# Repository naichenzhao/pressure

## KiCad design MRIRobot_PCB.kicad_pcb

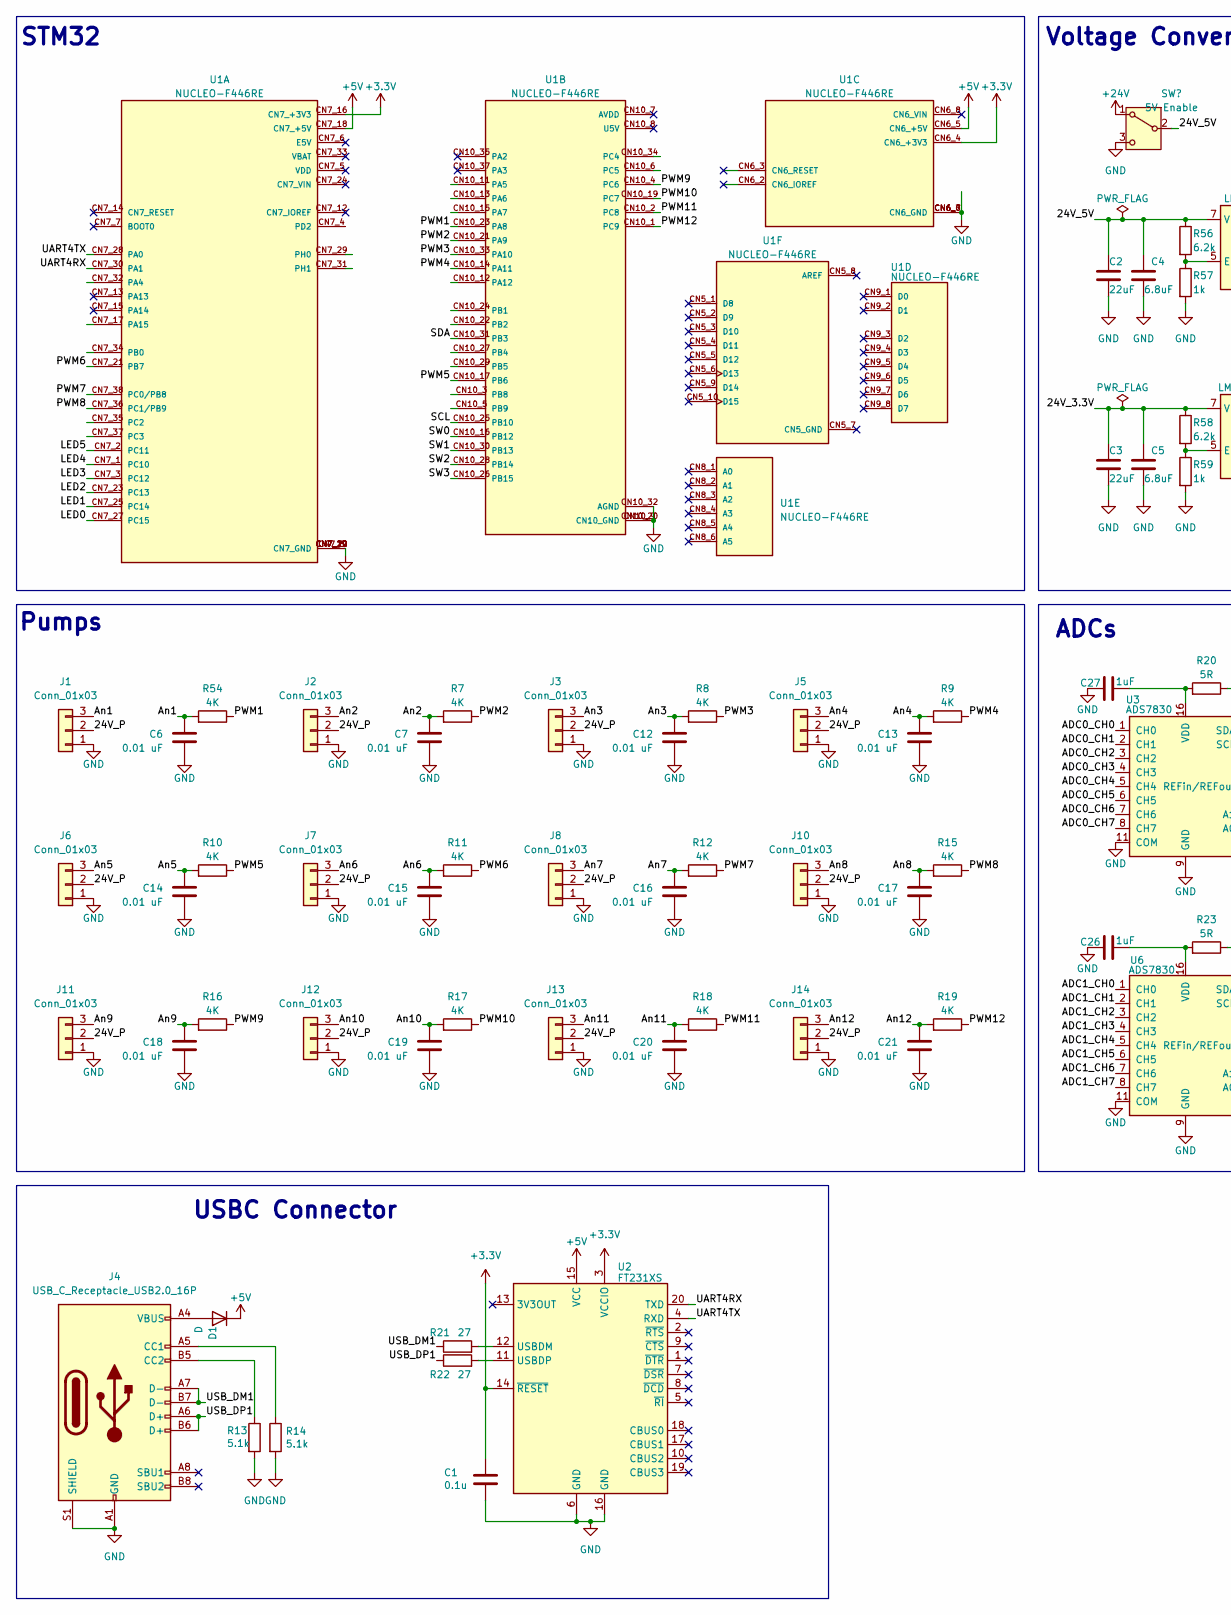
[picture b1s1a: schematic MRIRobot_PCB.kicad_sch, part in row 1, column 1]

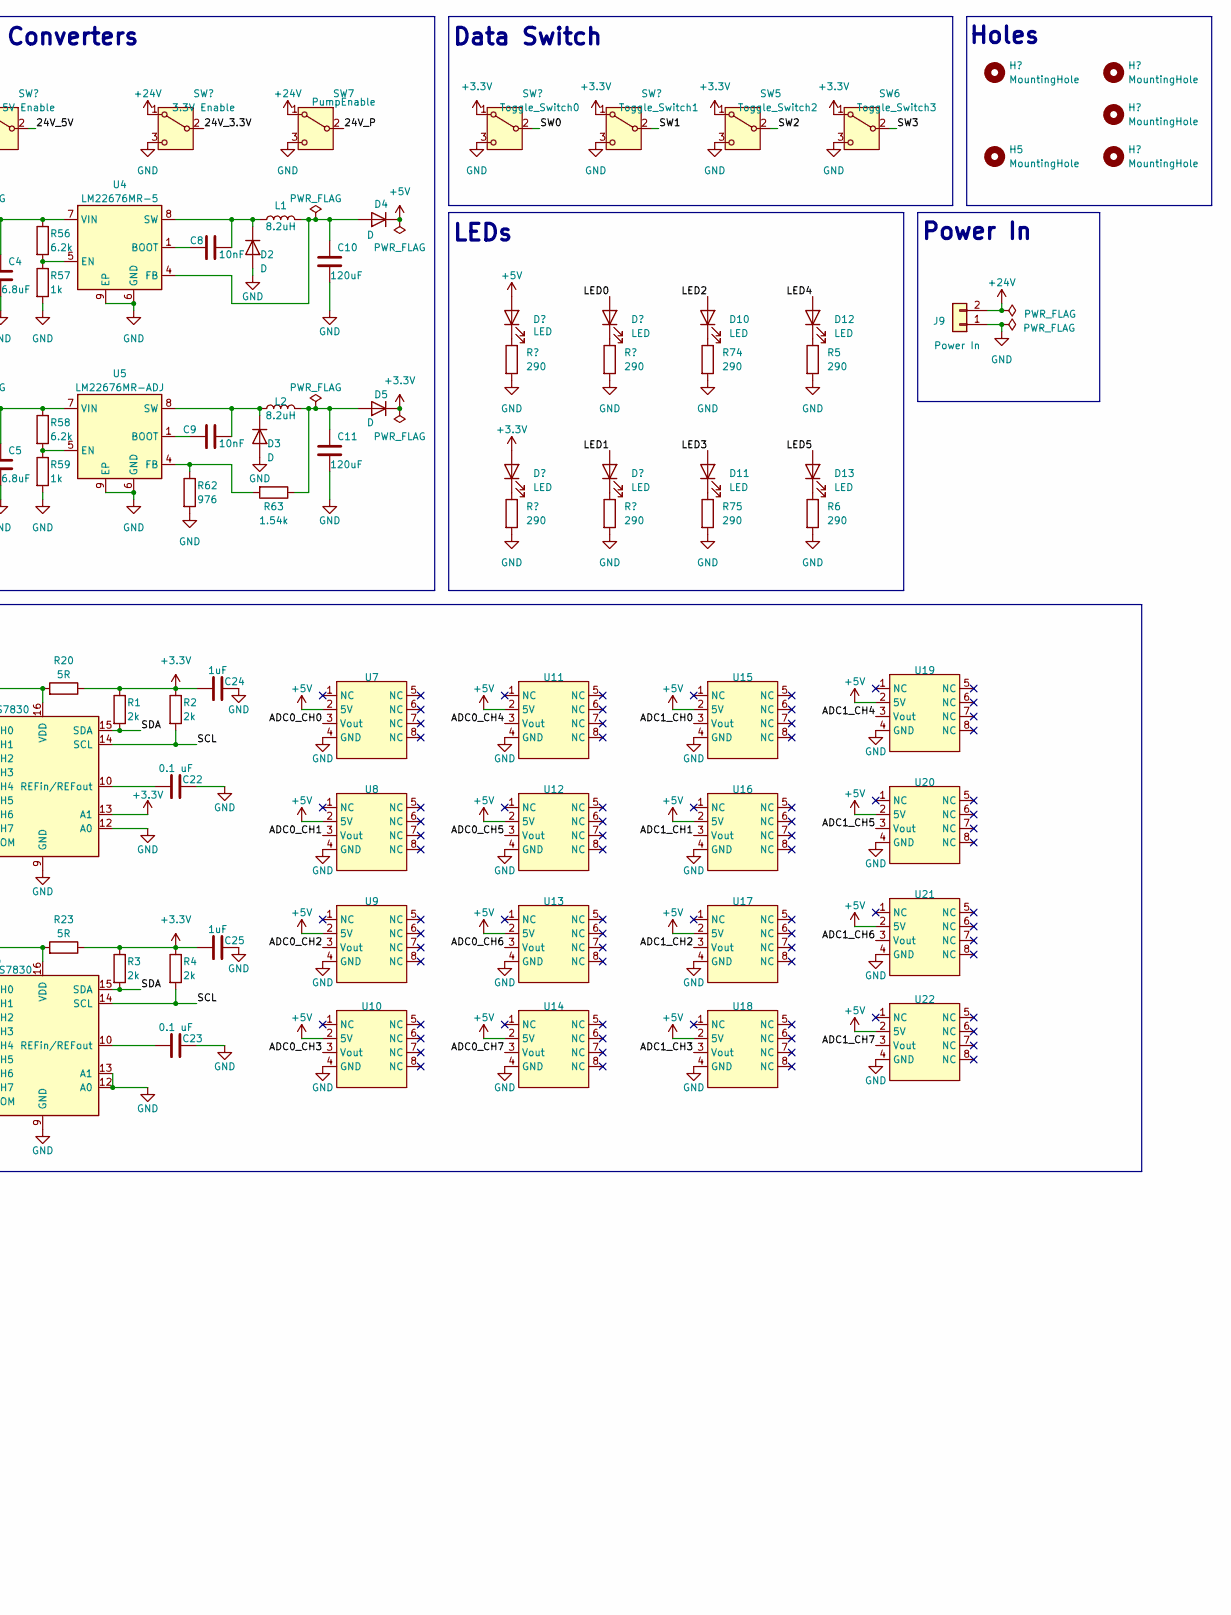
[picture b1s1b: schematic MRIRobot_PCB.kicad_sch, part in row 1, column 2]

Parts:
C1: 0.1u; C_0603_1608Metric_Pad1.08x0.95mm_HandSolder
C2, C3: 22uF; CP_Radial_D5.0mm_P2.00mm
C4, C5: 6.8uF; C_0805_2012Metric
C6, C7, C12, C13, C14, C15, C16, C17, C18, C19, C20, C21: 0.01 uF; C_0805_2012Metric_Pad1.18x1.45mm_HandSolder
C8, C9: 10nF; C_0805_2012Metric
C10, C11: 120uF; CP_Radial_D6.3mm_P2.50mm
C22, C23: 0.1 uF; C_0805_2012Metric_Pad1.18x1.45mm_HandSolder
C24, C25, C26, C27: 1uF; C_0805_2012Metric_Pad1.18x1.45mm_HandSolder
D1, D2, D3, D4, D5: D; D_SMA_Handsoldering
D6, D7, D8, D9, D10, D11, D12, D13: LED; LED_0805_2012Metric_Pad1.15x1.40mm_HandSolder
H1, H3, H4, H5, H6: MountingHole; MountingHole_3.2mm_M3
J1, J2, J3, J5, J6, J7, J8, J10, J11, J12, J13, J14: Conn_01x03; JST_XH_B3B-XH-AM_1x03_P2.50mm_Vertical
J4: USB_C_Receptacle_USB2.0_16P; USB_C_Receptacle_GCT_USB4105-xx-A_16P_TopMnt_Horizontal
J9: Power In; AMASS_XT60-M_1x02_P7.20mm_Vertical
L1, L2: 8.2uH; L_7.3x7.3_H3.5
R1, R2, R3, R4: 2k; R_0805_2012Metric
R5, R6, R68, R69, R70, R71, R74, R75: 290; C_0805_2012Metric_Pad1.18x1.45mm_HandSolder
R7, R8, R9, R10, R11, R12, R15, R16, R17, R18, R19, R54: 4K; C_0805_2012Metric_Pad1.18x1.45mm_HandSolder
R13, R14: 5.1k; R_0603_1608Metric_Pad0.98x0.95mm_HandSolder
R20, R23: 5R; C_0805_2012Metric_Pad1.18x1.45mm_HandSolder
R21, R22: 27; R_0603_1608Metric_Pad0.98x0.95mm_HandSolder
R56, R58: 6.2k; R_0805_2012Metric
R57, R59: 1k; R_0805_2012Metric
R62: 976; R_0805_2012Metric
R63: 1.54k; R_0805_2012Metric
SW1: 5V Enable; SW_Slide_SPDT_Straight_CK_OS102011MS2Q
SW2: 3.3V Enable; SW_Slide_SPDT_Straight_CK_OS102011MS2Q
SW3: Toggle_Switch0; SW_Slide_SPDT_Straight_CK_OS102011MS2Q
SW4: Toggle_Switch1; SW_Slide_SPDT_Straight_CK_OS102011MS2Q
SW5: Toggle_Switch2; SW_Slide_SPDT_Straight_CK_OS102011MS2Q
SW6: Toggle_Switch3; SW_Slide_SPDT_Straight_CK_OS102011MS2Q
SW7: PumpEnable; SW_Slide_SPDT_Straight_CK_OS102011MS2Q
U1: NUCLEO-F446RE; MODULE_NUCLEO-F446RE; PARTREV 13
U2: FT231XS; SSOP-20_3.9x8.7mm_P0.635mm
U3, U6: ADS7830; TSSOP-16_4.4x5mm_P0.65mm
U4: LM22676MR-5; TI_SO-PowerPAD-8
U5: LM22676MR-ADJ; TI_SO-PowerPAD-8
U7, U8, U9, U10, U11, U12, U13, U14, U15, U16, U17, U18, U19, U20, U21, U22: DIP-8_W7.62mm

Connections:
+3.3V: C1.1, C24.1, C25.1, D5.1 (K), D7.2 (A), R1.1, R2.1, R3.1, R4.1, R20.1, R23.1, SW3.1 (A), SW4.1 (A), SW5.1 (A), SW6.1 (A), U1.CN6_4 (CN6_+3V3), U1.CN7_16 (CN7_+3V3), U2.3 (VCCIO), U2.14 (~RESET), U3.13 (A1)
+5V: D1.1 (K), D4.1 (K), D6.2 (A), U1.CN6_5 (CN6_+5V), U1.CN7_18 (CN7_+5V), U2.15 (VCC), U7.2 (5V), U8.2 (5V), U9.2 (5V), U10.2 (5V), U11.2 (5V), U12.2 (5V), U13.2 (5V), U14.2 (5V), U15.2 (5V), U16.2 (5V), U17.2 (5V), U18.2 (5V), U19.2 (5V), U20.2 (5V), U21.2 (5V), U22.2 (5V)
+24V: J9.2, SW1.1 (A), SW2.1 (A), SW7.1 (A)
/24V_3.3V: C3.1, C5.1, R58.1, SW2.2 (B), U5.7 (VIN)
/24V_5V: C2.1, C4.1, R56.1, SW1.2 (B), U4.7 (VIN)
/24V_P: J1.2, J2.2, J3.2, J5.2, J6.2, J7.2, J8.2, J10.2, J11.2, J12.2, J13.2, J14.2, SW7.2 (B)
/ADC0_CH0: U3.1 (CH0), U7.3 (Vout)
/ADC0_CH1: U3.2 (CH1), U8.3 (Vout)
/ADC0_CH2: U3.3 (CH2), U9.3 (Vout)
/ADC0_CH3: U3.4 (CH3), U10.3 (Vout)
/ADC0_CH4: U3.5 (CH4), U11.3 (Vout)
/ADC0_CH5: U3.6 (CH5), U12.3 (Vout)
/ADC0_CH6: U3.7 (CH6), U13.3 (Vout)
/ADC0_CH7: U3.8 (CH7), U14.3 (Vout)
/ADC1_CH0: U6.1 (CH0), U15.3 (Vout)
/ADC1_CH1: U6.2 (CH1), U16.3 (Vout)
/ADC1_CH2: U6.3 (CH2), U17.3 (Vout)
/ADC1_CH3: U6.4 (CH3), U18.3 (Vout)
/ADC1_CH4: U6.5 (CH4), U19.3 (Vout)
/ADC1_CH5: U6.6 (CH5), U20.3 (Vout)
/ADC1_CH6: U6.7 (CH6), U21.3 (Vout)
/ADC1_CH7: U6.8 (CH7), U22.3 (Vout)
/An1: C6.1, J1.3, R54.2
/An2: C7.1, J2.3, R7.2
/An3: C12.1, J3.3, R8.2
/An4: C13.1, J5.3, R9.2
/An5: C14.1, J6.3, R10.2
/An6: C15.1, J7.3, R11.2
/An7: C16.1, J8.3, R12.2
/An8: C17.1, J10.3, R15.2
/An9: C18.1, J11.3, R16.2
/An10: C19.1, J12.3, R17.2
/An11: C20.1, J13.3, R18.2
/An12: C21.1, J14.3, R19.2
/LED0: D8.2 (A), U1.CN7_27 (PC15)
/LED1: D9.2 (A), U1.CN7_25 (PC14)
/LED2: D10.2 (A), U1.CN7_23 (PC13)
/LED3: D11.2 (A), U1.CN7_3 (PC12)
/LED4: D12.2 (A), U1.CN7_1 (PC10)
/LED5: D13.2 (A), U1.CN7_2 (PC11)
/PWM1: R54.1, U1.CN10_23 (PA8)
/PWM2: R7.1, U1.CN10_21 (PA9)
/PWM3: R8.1, U1.CN10_33 (PA10)
/PWM4: R9.1, U1.CN10_14 (PA11)
/PWM5: R10.1, U1.CN10_17 (PB6)
/PWM6: R11.1, U1.CN7_21 (PB7)
/PWM7: R12.1, U1.CN7_38 (PC0/PB8)
/PWM8: R15.1, U1.CN7_36 (PC1/PB9)
/PWM9: R16.1, U1.CN10_4 (PC6)
/PWM10: R17.1, U1.CN10_19 (PC7)
/PWM11: R18.1, U1.CN10_2 (PC8)
/PWM12: R19.1, U1.CN10_1 (PC9)
/SCL: R2.2, R4.2, U1.CN10_25 (PB10), U3.14 (SCL), U6.14 (SCL)
/SDA: R1.2, R3.2, U1.CN10_31 (PB3), U3.15 (SDA), U6.15 (SDA)
/SW0: SW3.2 (B), U1.CN10_16 (PB12)
/SW1: SW4.2 (B), U1.CN10_30 (PB13)
/SW2: SW5.2 (B), U1.CN10_28 (PB14)
/SW3: SW6.2 (B), U1.CN10_26 (PB15)
/UART4RX: U1.CN7_30 (PA1), U2.20 (TXD)
/UART4TX: U1.CN7_28 (PA0), U2.4 (RXD)
/USB_DM1: J4.A7 (D-), J4.B7 (D-), R21.1
/USB_DP1: J4.A6 (D+), J4.B6 (D+), R22.1
GND: C1.2, C2.2, C3.2, C4.2, C5.2, C6.2, C7.2, C10.2, C11.2, C12.2, C13.2, C14.2, C15.2, C16.2, C17.2, C18.2, C19.2, C20.2, C21.2, C22.2, C23.2, C24.2, C25.2, C26.2, C27.2, D2.2 (A), D3.2 (A), J1.1, J2.1, J3.1, J4.A1 (GND), J4.A12 (GND), J4.B1 (GND), J4.B12 (GND), J4.S1 (SHIELD), J5.1, J6.1, J7.1, J8.1, J9.1, J10.1, J11.1, J12.1, J13.1, J14.1, R5.2, R6.2, R13.2, R14.2, R57.2, R59.2, R62.2, R68.2, R69.2, R70.2, R71.2, R74.2, R75.2, SW1.3 (C), SW2.3 (C), SW3.3 (C), SW4.3 (C), SW5.3 (C), SW6.3 (C), SW7.3 (C), U1.CN6_6 (CN6_GND), U1.CN6_7 (CN6_GND), U1.CN7_8 (CN7_GND), U1.CN7_19 (CN7_GND), U1.CN7_20 (CN7_GND), U1.CN7_22 (CN7_GND), U1.CN10_9 (CN10_GND), U1.CN10_20 (CN10_GND), U1.CN10_32 (AGND), U2.6 (GND), U2.16 (GND), U3.9 (GND), U3.11 (COM), U3.12 (A0), U4.6 (GND), U4.9 (EP), U5.6 (GND), U5.9 (EP), U6.9 (GND), U6.11 (COM), U6.12 (A0), U6.13 (A1), U7.4 (GND), U8.4 (GND), U9.4 (GND), U10.4 (GND), U11.4 (GND), U12.4 (GND), U13.4 (GND), U14.4 (GND), U15.4 (GND), U16.4 (GND), U17.4 (GND), U18.4 (GND), U19.4 (GND), U20.4 (GND), U21.4 (GND), U22.4 (GND)
unnamed: D1.2 (A), J4.A4 (VBUS), J4.A9 (VBUS), J4.B4 (VBUS), J4.B9 (VBUS)
unnamed: C8.2, D2.1 (K), L1.1, U4.8 (SW)
unnamed: C9.2, D3.1 (K), L2.1, U5.8 (SW)
unnamed: C10.1, D4.2 (A), L1.2, U4.4 (FB)
unnamed: C11.1, D5.2 (A), L2.2, R63.1
unnamed: D6.1 (K), R68.1
unnamed: D7.1 (K), R69.1
unnamed: D8.1 (K), R70.1
unnamed: D9.1 (K), R71.1
unnamed: D10.1 (K), R74.1
unnamed: D11.1 (K), R75.1
unnamed: D12.1 (K), R5.1
unnamed: D13.1 (K), R6.1
unnamed: J4.A5 (CC1), R14.1
unnamed: J4.B5 (CC2), R13.1
unnamed: R21.2, U2.12 (USBDM)
unnamed: R22.2, U2.11 (USBDP)
unnamed: C22.1, U3.10 (REFin/REFout)
unnamed: C27.1, R20.2, U3.16 (VDD)
unnamed: C8.1, U4.1 (BOOT)
unnamed: R56.2, R57.1, U4.5 (EN)
unnamed: C9.1, U5.1 (BOOT)
unnamed: R58.2, R59.1, U5.5 (EN)
unnamed: R62.1, R63.2, U5.4 (FB)
unnamed: C23.1, U6.10 (REFin/REFout)
unnamed: C26.1, R23.2, U6.16 (VDD)

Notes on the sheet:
Holes
STM32
LEDs
Data Switch
USBC Connector
ADCs
Power In
Pumps
Voltage Converters

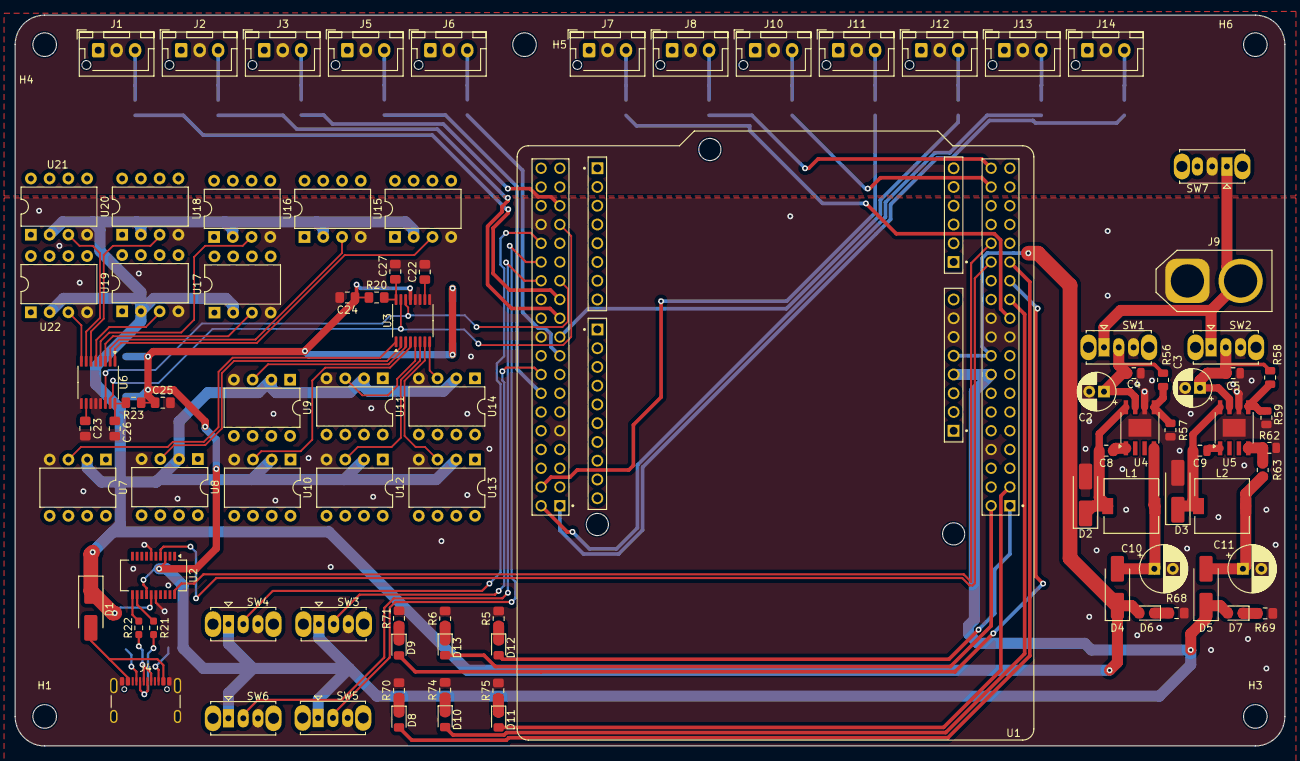
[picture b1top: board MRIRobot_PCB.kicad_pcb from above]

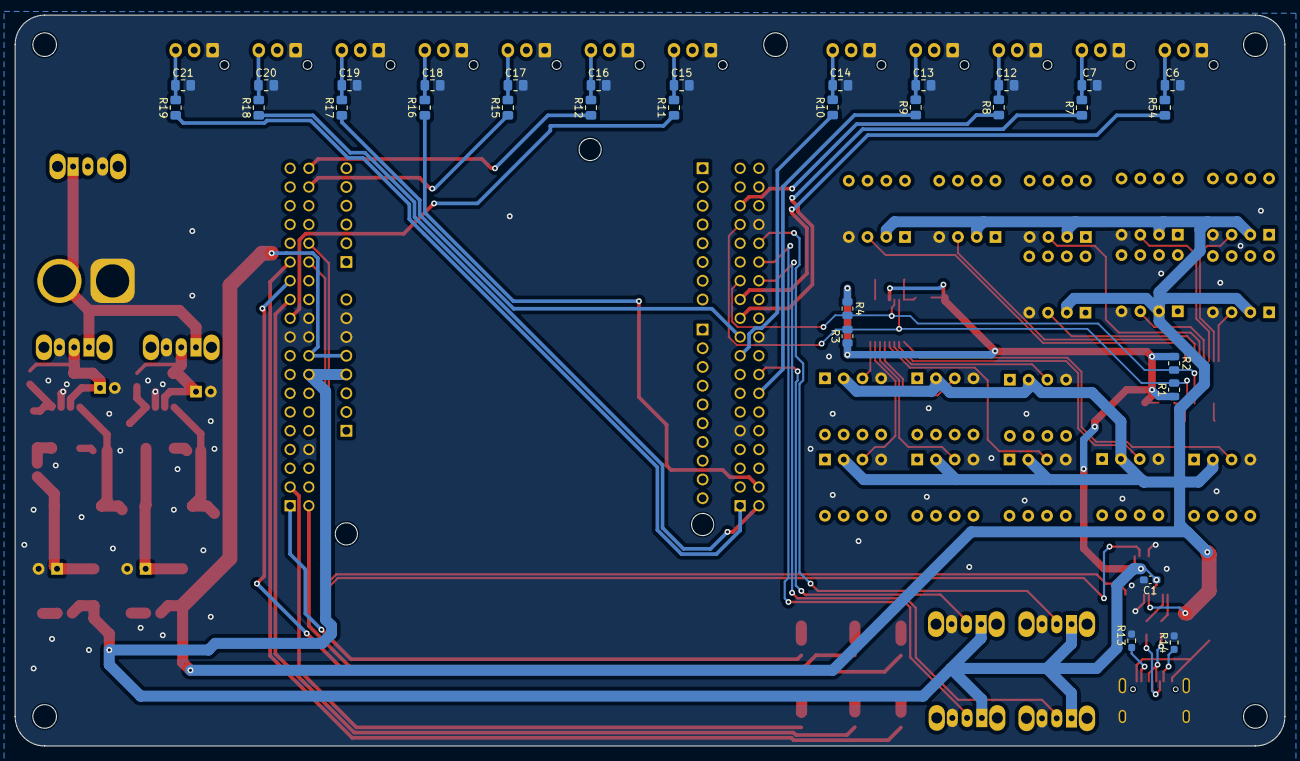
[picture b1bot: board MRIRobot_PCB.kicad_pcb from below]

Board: 2 copper layers, 172.0 x 99.0 mm, 126 parts (31 on the bottom side), 89 nets.

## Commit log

2024-10-02 all code
2024-10-02 added gerber
